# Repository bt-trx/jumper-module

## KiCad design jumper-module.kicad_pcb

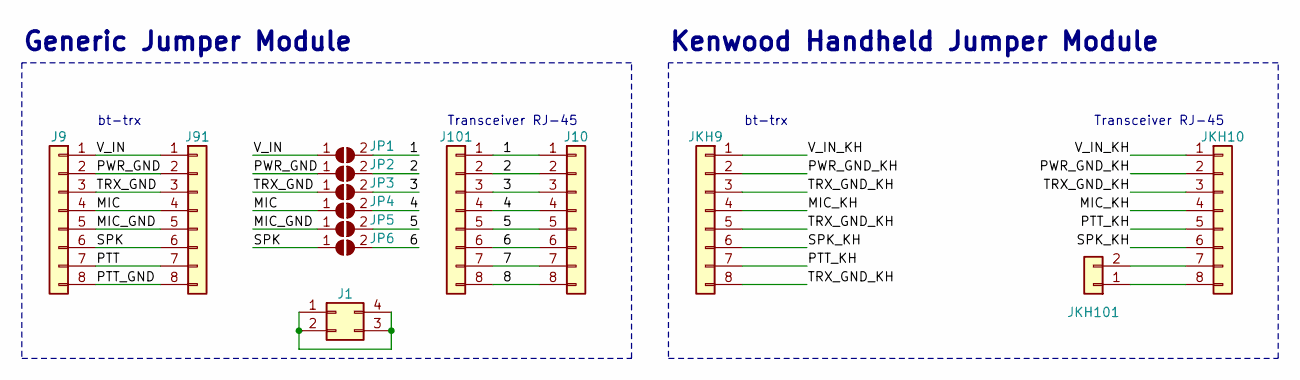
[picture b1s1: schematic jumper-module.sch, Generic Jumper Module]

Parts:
J1: PinHeader_2x02_P2.54mm_Vertical
J9, J10: Conn_01x08; PinHeader_1x08_P2.54mm_Vertical; Mouser-Best. Nr 649-68000-408HLF
J91, J101: Conn_01x08; PinHeader_1x08_P2.54mm_Vertical
JKH9, JKH10: Conn_01x08; PinHeader_1x08_P2.54mm_Vertical; Mouser-Best. Nr 649-68000-408HLF
JKH101: Conn_01x02; PinHeader_1x02_P2.54mm_Vertical
JP1, JP2, JP3, JP4, JP5, JP6: SolderJumper_2_Open; SolderJumper-2_P1.3mm_Open_TrianglePad1.0x1.5mm

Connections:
/1: J10.1, J101.1, JP1.2 (B)
/2: J10.2, J101.2, JP2.2 (B)
/3: J10.3, J101.3, JP3.2 (B)
/4: J10.4, J101.4, JP4.2 (B)
/5: J10.5, J101.5, JP5.2 (B)
/6: J10.6, J101.6, JP6.2 (B)
/7: J10.7, J101.7
/8: J10.8, J101.8
/MIC: J9.4, J91.4, JP4.1 (A)
/MIC_GND: J9.5, J91.5, JP5.1 (A)
/MIC_KH: JKH9.4, JKH10.4
/PTT: J9.7, J91.7
/PTT_GND: J9.8, J91.8
/PTT_KH: JKH9.7, JKH10.5
/PWR_GND: J9.2, J91.2, JP2.1 (A)
/PWR_GND_KH: JKH9.2, JKH10.2
/SPK: J9.6, J91.6, JP6.1 (A)
/SPK_KH: JKH9.6, JKH10.6
/TRX_GND: J9.3, J91.3, JP3.1 (A)
/TRX_GND_KH: JKH9.3, JKH9.5, JKH9.8, JKH10.3
/V_IN: J9.1, J91.1, JP1.1 (A)
/V_IN_KH: JKH9.1, JKH10.1
unnamed: J1.1, J1.2, J1.3, J1.4
unnamed: JKH10.7, JKH101.2
unnamed: JKH10.8, JKH101.1

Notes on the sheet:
Transceiver RJ-45
bt-trx
Generic Jumper Module
Kenwood Handheld Jumper Module

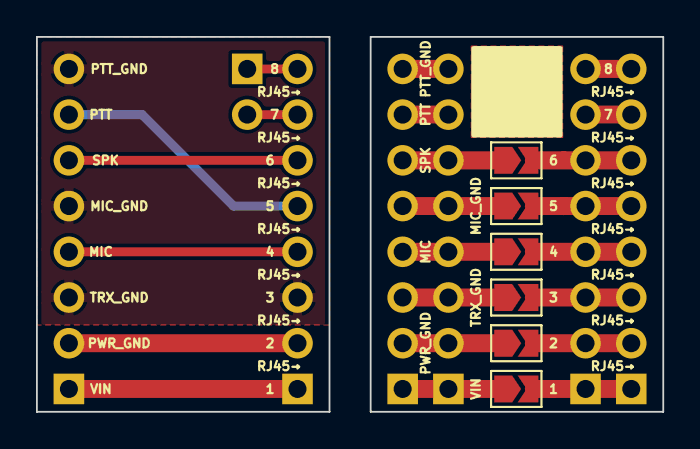
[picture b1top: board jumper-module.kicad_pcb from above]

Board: 2 copper layers, 34.8 x 20.8 mm, 14 parts (0 on the bottom side), 25 nets.

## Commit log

2020-01-17 Add LICENSE.md
2020-01-17 Add schematic for generic jumper module
2020-01-21 Created Generic Daughterboard
    * connected 1-6 via solder jumper
    * created 2x2 field for bridging GND
2020-01-21 Added 3D Models
2020-01-22 Added bottom silkscreen and changed board size
2020-01-22 Added BOM
2020-01-22 Added Gerber files
2020-02-23 Non generic Handheld JM
    Created first verion of non generic handheld jumper module
    for kenwood handhelds

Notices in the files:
jumper-module.kicad_pcb:
Licensed under CERN OHL v1.2 - https://ohwr.org/licenses/cern-ohl/v1.2
